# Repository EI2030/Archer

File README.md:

Archer is the codename of our 1st EPD laptop prototype with custom-designed motherboard and 3D-printed chassis.

# Specifications

The specification listed are preliminary and subject to change. Note this is only the specification for the prototype, it does **not** represent the spec for the final product.

- SoC: NXP i.MX 7Dual (2x ARM Cortex-A7 @ 1.2GHz)
- RAM: 2x Micron MT41K256M16 (1GB in total, DDR3)
- Flash: None (prototype designed to always boots from TF card)
- HDD: None
- Network: RTL8273BS (802.11n + BT)
- Main Screen: E Ink ED103TC2 (10.3" 1872x1404) with capactive touch screen
- Sub Screen: ER-TFT0784-1 (7.84" 1280x400) with capactive touch screen
- Screen Controller: i.MX7 integrated EPDC
- Battery: 2x User replaceable LiFePO4 18650 battery
- EC: LPC55S28
- Ports:
  - USB 2.0 Type A Host x1
  - USB 2.0 Type C UFP with Power Delivery x1
  - USB 2.0 Micro B Serial Debug Console x1
  - TF card slot

# Goals

## Goals of this prototype

- Proof of Concept of a EPD laptop
- Enable early development of EC firmware
- Enable early development of the user software
- Test chassis design ideas
- Verify peripheral circuit design
- Enable future prototype with final processor choice

## Non-Goals

- Archer will not represent the performance level of the final product
- Archer is not optimized for low power consumption

# Progress

## Chassis

R0.1 chassis design in progress. Not yet printed.

## Motherboard

R0.1 PCB design finished. Sent to fab.

# Legalese

E Ink® is a registered trademark by E Ink Corporation. All other trademarks are property of their respective owner.

# License

The hardware design is released under the CERN Open Source Hardware License strongly-reciprocal variant, CERN-OHL-S. A copy of the license is provided in the source repository. Additionally, user guide of the license is provided on ohwr.org.

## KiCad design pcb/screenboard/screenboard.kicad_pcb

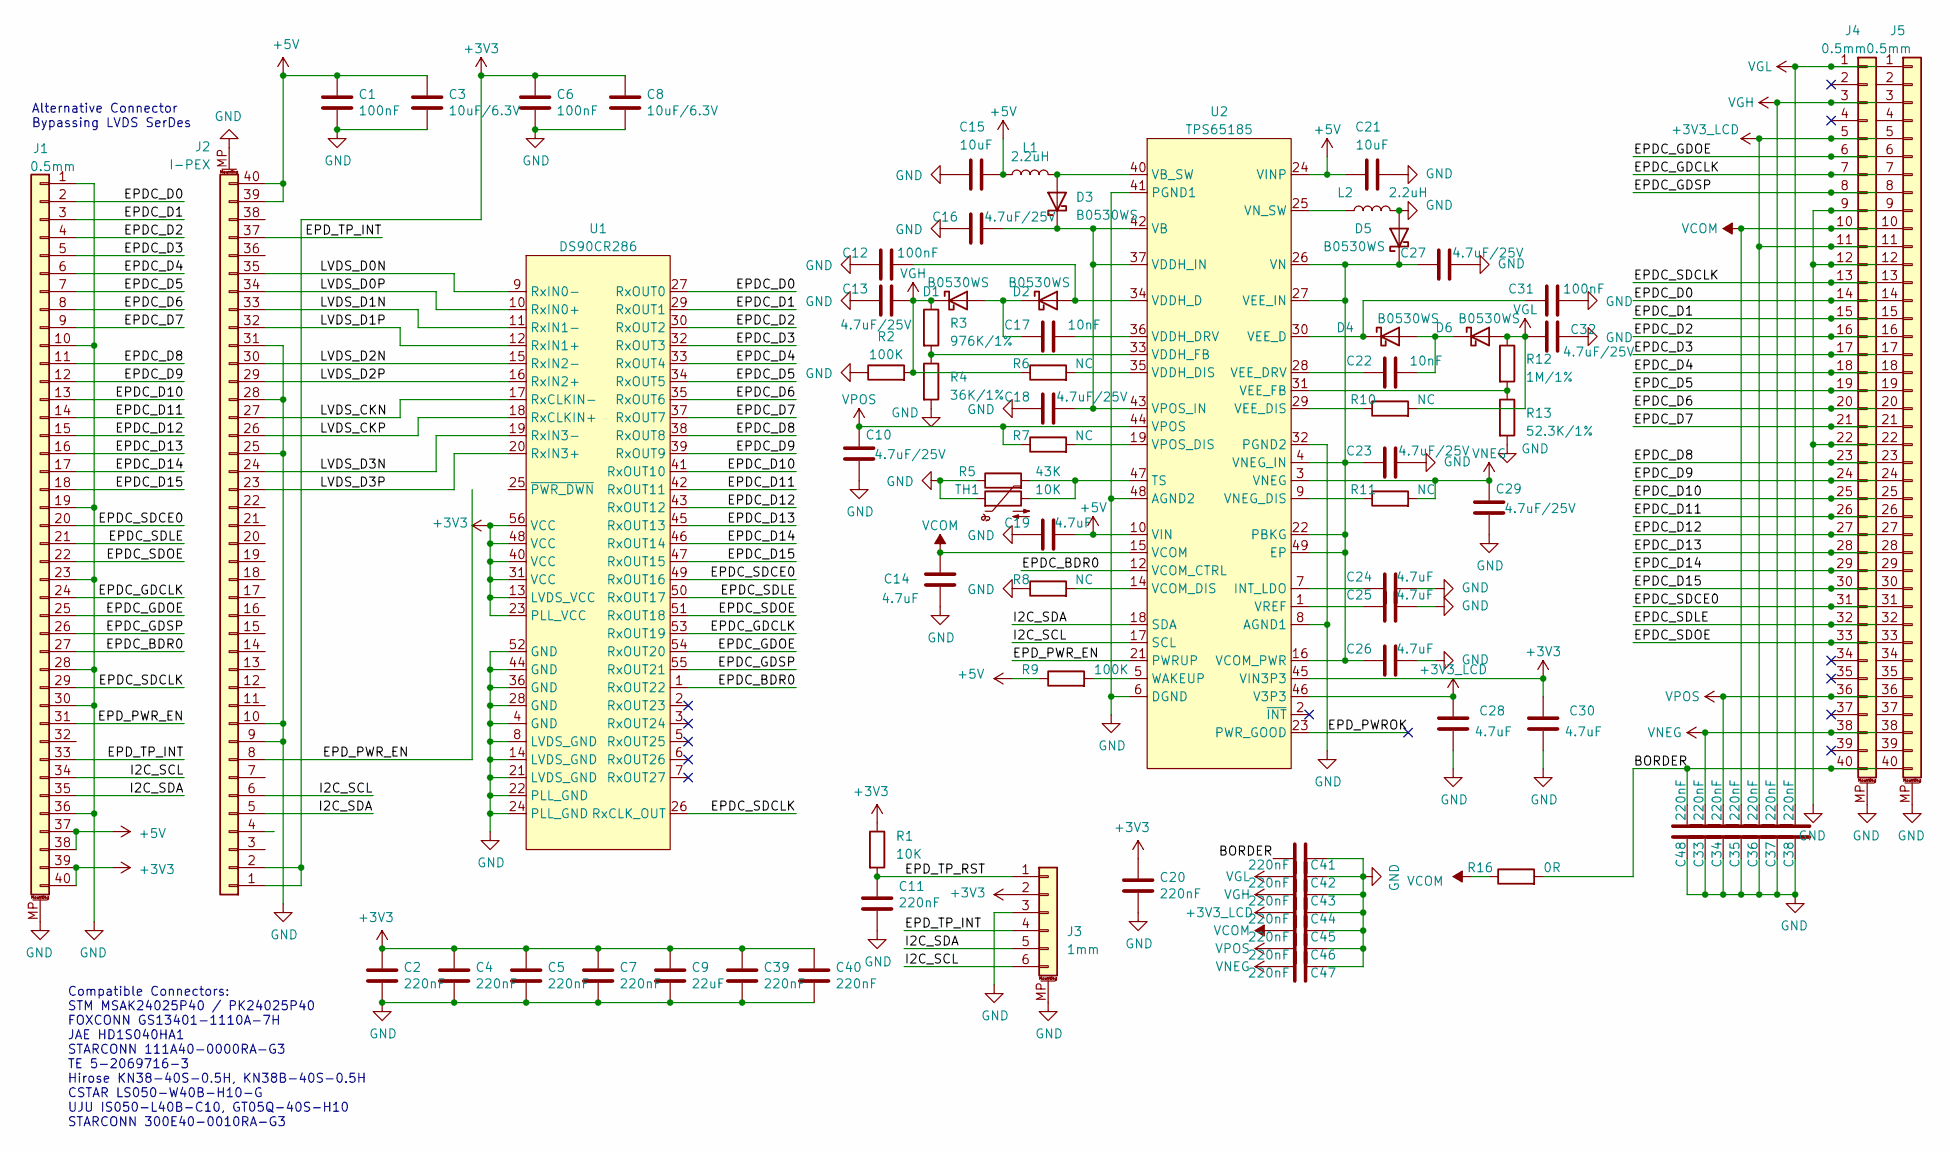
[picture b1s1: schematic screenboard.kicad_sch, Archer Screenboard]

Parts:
C1, C6, C12, C31: 100nF; C_0402_1005Metric
C2, C4, C5, C7, C11, C20, C33, C34, C35, C36, C37, C38, C39, C40, C41, C42, C43, C44, C45, C46, C47, C48: 220nF; C_0402_1005Metric
C3, C8: 10uF/6.3V; C_0603_1608Metric
C9: 22uF; C_0603_1608Metric
C10, C13, C16, C18, C23, C27, C29, C32: 4.7uF/25V; C_0805_2012Metric
C14, C19, C24, C25, C26, C28, C30: 4.7uF; C_0603_1608Metric
C15, C21: 10uF; C_0603_1608Metric
C17, C22: 10nF; C_0402_1005Metric
D1, D2, D3, D4, D5, D6: B0530WS; D_SOD-323
J1: 0.5mm; Hirose_FH12-40S-0.5SH_1x40-1MP_P0.50mm_Horizontal
J2: I-PEX; TE_5-2069716-3_1x40-1MP_P0.5mm_Horizontal
J3: 1mm; Molex_200528-0060_1x06-1MP_P1.00mm_Horizontal_Reversed
J4, J5: 0.5mm; Hirose_FH12-40S-0.5SH_1x40-1MP_P0.50mm_Horizontal_Reversed
L1, L2: 2.2uH; L_Vishay_IHLP-1212
R1: 10K; R_0402_1005Metric
R2, R9: 100K; R_0402_1005Metric
R3: 976K/1%; R_0402_1005Metric
R4: 36K/1%; R_0402_1005Metric
R5: 43K; R_0402_1005Metric
R6, R7, R8, R10, R11: NC; R_0402_1005Metric
R12: 1M/1%; R_0402_1005Metric
R13: 52.3K/1%; R_0402_1005Metric
R16: 0R; R_0402_1005Metric
TH1: 10K; R_0402_1005Metric
U1: DS90CR286; TSSOP-56_6.1x14mm_P0.5mm
U2: TPS65185; QFN-48-1EP_7x7mm_P0.5mm_EP4.1x4.1mm_ThermalVias

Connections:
+3V3: C2.1, C4.1, C5.1, C6.1, C7.1, C8.1, C9.1, C20.1, C30.1, C39.1, C40.1, J1.39, J1.40, J2.1, J2.2, J3.2, R1.1, U1.13 (LVDS_VCC), U1.23 (PLL_VCC), U1.31 (VCC), U1.40 (VCC), U1.48 (VCC), U1.56 (VCC), U2.45 (VIN3P3)
+3V3_LCD: C28.1, C36.1, C44.1, J4.5, J4.11, J5.5, J5.11, U2.46 (V3P3)
+5V: C1.1, C3.1, C15.2, C19.2, C21.1, J1.37, J1.38, J2.39, J2.40, L1.1, R9.1, U2.10 (VIN), U2.24 (VINP)
/BORDER: C41.1, C48.1, J4.40, J5.40, R16.2
/EPDC_BDR0: J1.27, U1.1 (RxOUT22), U2.12 (VCOM_CTRL)
/EPDC_D0: J1.2, J4.14, J5.14, U1.27 (RxOUT0)
/EPDC_D1: J1.3, J4.15, J5.15, U1.29 (RxOUT1)
/EPDC_D2: J1.4, J4.16, J5.16, U1.30 (RxOUT2)
/EPDC_D3: J1.5, J4.17, J5.17, U1.32 (RxOUT3)
/EPDC_D4: J1.6, J4.18, J5.18, U1.33 (RxOUT4)
/EPDC_D5: J1.7, J4.19, J5.19, U1.34 (RxOUT5)
/EPDC_D6: J1.8, J4.20, J5.20, U1.35 (RxOUT6)
/EPDC_D7: J1.9, J4.21, J5.21, U1.37 (RxOUT7)
/EPDC_D8: J1.11, J4.23, J5.23, U1.38 (RxOUT8)
/EPDC_D9: J1.12, J4.24, J5.24, U1.39 (RxOUT9)
/EPDC_D10: J1.13, J4.25, J5.25, U1.41 (RxOUT10)
/EPDC_D11: J1.14, J4.26, J5.26, U1.42 (RxOUT11)
/EPDC_D12: J1.15, J4.27, J5.27, U1.43 (RxOUT12)
/EPDC_D13: J1.16, J4.28, J5.28, U1.45 (RxOUT13)
/EPDC_D14: J1.17, J4.29, J5.29, U1.46 (RxOUT14)
/EPDC_D15: J1.18, J4.30, J5.30, U1.47 (RxOUT15)
/EPDC_GDCLK: J1.24, J4.7, J5.7, U1.53 (RxOUT19)
/EPDC_GDOE: J1.25, J4.6, J5.6, U1.54 (RxOUT20)
/EPDC_GDSP: J1.26, J4.8, J5.8, U1.55 (RxOUT21)
/EPDC_SDCE0: J1.20, J4.31, J5.31, U1.49 (RxOUT16)
/EPDC_SDCLK: J1.29, J4.13, J5.13, U1.26 (RxCLK_OUT)
/EPDC_SDLE: J1.21, J4.32, J5.32, U1.50 (RxOUT17)
/EPDC_SDOE: J1.22, J4.33, J5.33, U1.51 (RxOUT18)
/EPD_PWR_EN: J1.31, J2.8, U2.21 (PWRUP)
/EPD_TP_INT: J1.33, J2.37, J3.4
/EPD_TP_RST: C11.1, J3.1, R1.2
/I2C_SCL: J1.34, J2.6, J3.6, U2.17 (SCL)
/I2C_SDA: J1.35, J2.5, J3.5, U2.18 (SDA)
/LVDS_CKN: J2.27, U1.17 (RxCLKIN-)
/LVDS_CKP: J2.26, U1.18 (RxCLKIN+)
/LVDS_D0N: J2.35, U1.9 (RxIN0-)
/LVDS_D0P: J2.34, U1.10 (RxIN0+)
/LVDS_D1N: J2.33, U1.11 (RxIN1-)
/LVDS_D1P: J2.32, U1.12 (RxIN1+)
/LVDS_D2N: J2.30, U1.15 (RxIN2-)
/LVDS_D2P: J2.29, U1.16 (RxIN2+)
/LVDS_D3N: J2.24, U1.19 (RxIN3-)
/LVDS_D3P: J2.23, U1.20 (RxIN3+)
GND: C1.2, C2.2, C3.2, C4.2, C5.2, C6.2, C7.2, C8.2, C9.2, C10.1, C11.2, C12.1, C13.1, C14.1, C15.1, C16.1, C18.1, C19.1, C20.2, C21.2, C23.2, C24.2, C25.2, C26.2, C27.2, C28.2, C29.1, C30.2, C31.2, C32.1, C33.2, C34.2, C35.2, C36.2, C37.2, C38.2, C39.2, C40.2, C41.2, C42.2, C43.2, C44.2, C45.2, C46.2, C47.2, C48.2, D5.2 (A), J1.1, J1.10, J1.19, J1.23, J1.28, J1.30, J1.36, J1.MP (MountPin), J2.9, J2.10, J2.25, J2.28, J2.31, J2.MP (MountPin), J3.3, J3.MP (MountPin), J4.9, J4.12, J4.22, J4.MP (MountPin), J5.9, J5.12, J5.22, J5.MP (MountPin), L2.2, R2.1, R4.2, R5.1, R8.1, R13.2, TH1.1, U1.4 (GND), U1.8 (LVDS_GND), U1.14 (LVDS_GND), U1.21 (LVDS_GND), U1.22 (PLL_GND), U1.24 (PLL_GND), U1.28 (GND), U1.36 (GND), U1.44 (GND), U1.52 (GND), U2.6 (DGND), U2.8 (AGND1), U2.32 (PGND2), U2.41 (PGND1), U2.48 (AGND2)
unnamed: C12.2, D2.2 (A), U2.34 (VDDH_D)
unnamed: C16.2, C18.2, D3.1 (K), U2.37 (VDDH_IN), U2.42 (VB), U2.43 (VPOS_IN)
unnamed: C17.1, D1.2 (A), D2.1 (K)
unnamed: C17.2, U2.36 (VDDH_DRV)
unnamed: C22.1, U2.28 (VEE_DRV)
unnamed: C22.2, D4.2 (A), D6.1 (K)
unnamed: C23.1, C26.1, C27.1, D5.1 (K), U2.4 (VNEG_IN), U2.16 (VCOM_PWR), U2.22 (PBKG), U2.26 (VN), U2.27 (VEE_IN), U2.49 (EP)
unnamed: C24.1, U2.7 (INT_LDO)
unnamed: C25.1, U2.1 (VREF)
unnamed: C31.1, D4.1 (K), U2.30 (VEE_D)
unnamed: D3.2 (A), L1.2, U2.40 (VB_SW)
unnamed: L2.1, U2.25 (VN_SW)
unnamed: R3.2, R4.1, U2.33 (VDDH_FB)
unnamed: R5.2, TH1.2, U2.47 (TS)
unnamed: R6.2, U2.35 (VDDH_DIS)
unnamed: R7.2, U2.19 (VPOS_DIS)
unnamed: R8.2, U2.14 (VCOM_DIS)
unnamed: R9.2, U2.5 (WAKEUP)
unnamed: R10.1, U2.29 (VEE_DIS)
unnamed: R11.1, U2.9 (VNEG_DIS)
unnamed: R12.2, R13.1, U2.31 (VEE_FB)
VCOM: C14.2, C35.1, C45.1, J4.10, J5.10, R16.1, U2.15 (VCOM)
VGH: C13.2, C37.1, C43.1, D1.1 (K), J4.3, J5.3, R2.2, R3.1, R6.1
VGL: C32.2, C38.1, C42.1, D6.2 (A), J4.1, J5.1, R10.2, R12.1
VNEG: C29.2, C33.1, C47.1, J4.38, J5.38, R11.2, U2.3 (VNEG)
VPOS: C10.2, C34.1, C46.1, J4.36, J5.36, R7.1, U2.44 (VPOS)

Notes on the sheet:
Alternative Connector Bypassing LVDS SerDes
Compatible Connectors: STM MSAK24025P40 / PK24025P40 FOXCONN GS13401-1110A-7H JAE HD1S040HA1 STARCONN 111A40-0000RA-G3 TE 5-2069716-3 Hirose KN38-40S-0.5H, KN38B-40S-0.5H CSTAR LS050-W40B-H10-G UJU IS050-L40B-C10, GT05Q-40S-H10 STARCONN 300E40-0010RA-G3

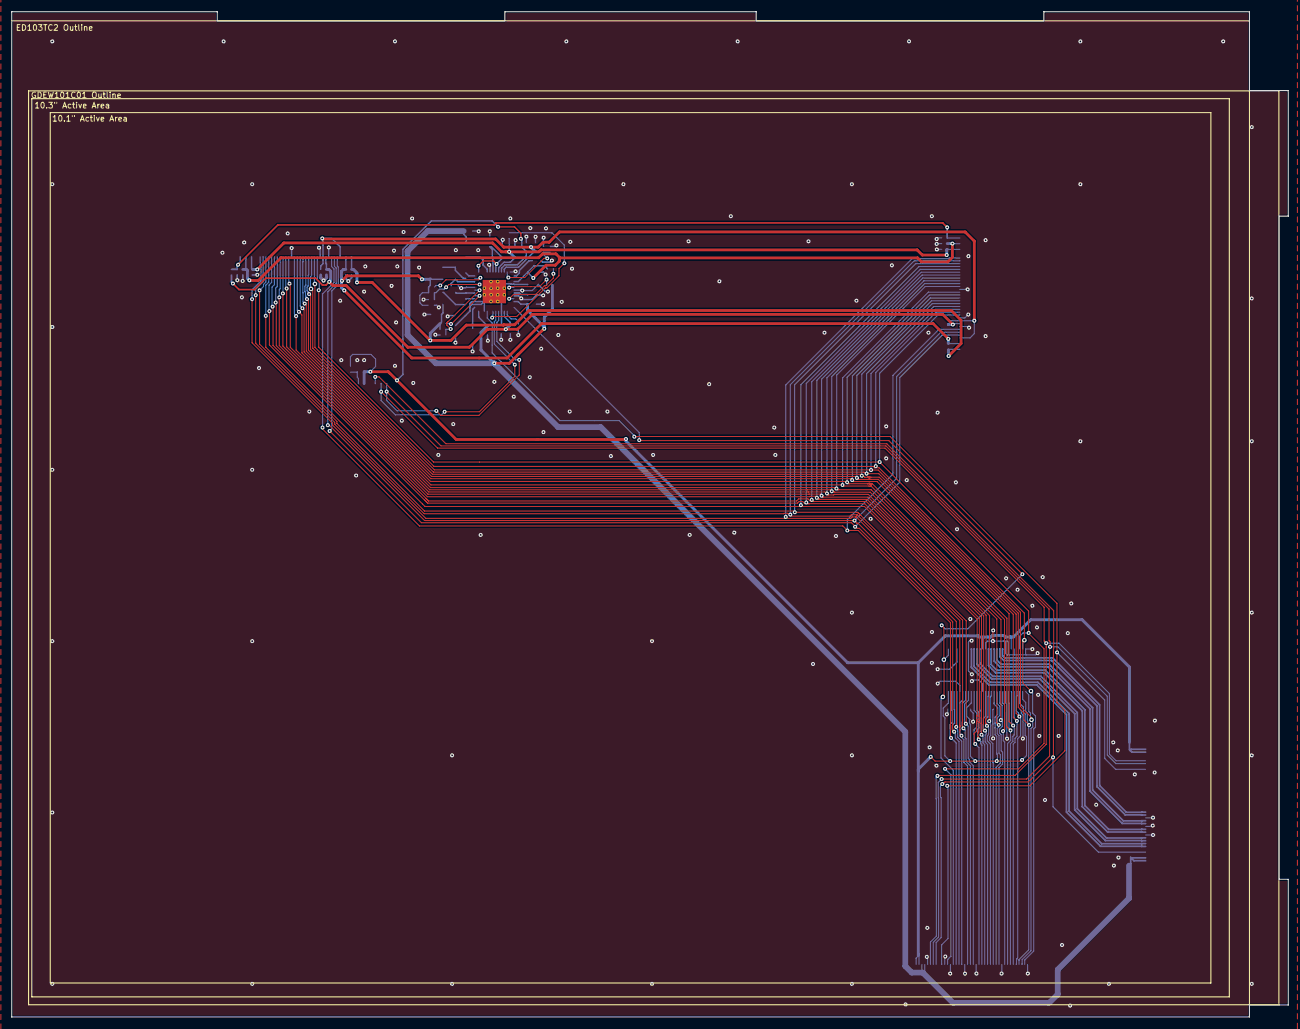
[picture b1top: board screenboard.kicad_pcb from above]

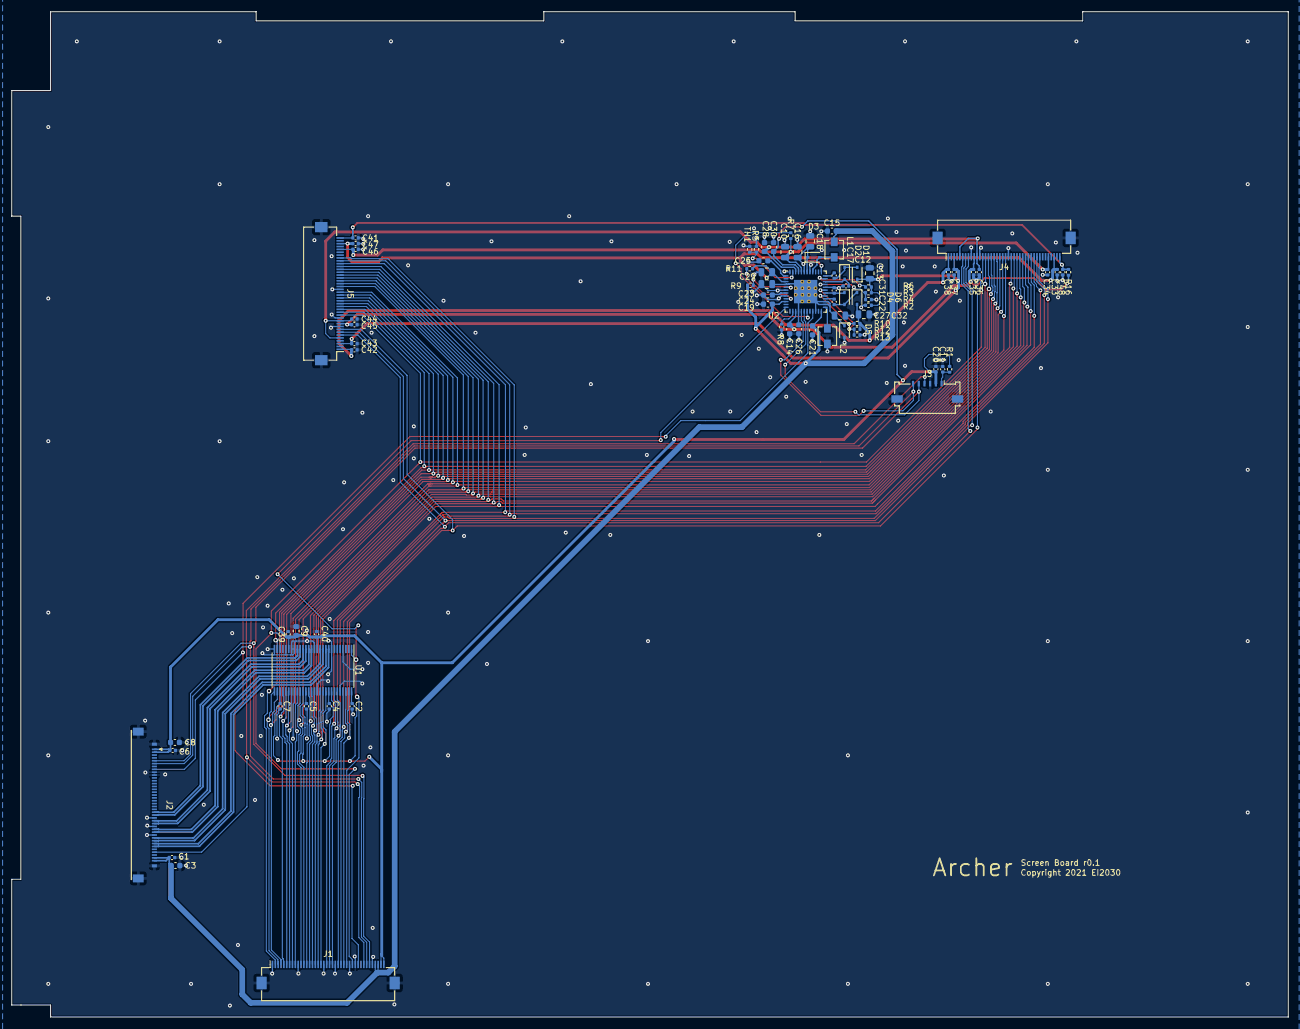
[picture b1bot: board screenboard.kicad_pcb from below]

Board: 2 copper layers, 223.5 x 176.0 mm, 78 parts (78 on the bottom side), 70 nets.

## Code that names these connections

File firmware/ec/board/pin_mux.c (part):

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mcu_data: ksdk2_0
processor_version: 9.0.1
pin_labels:
- {pin_num: '54', pin_signal: PIO0_0/FC3_SCK/CTIMER0_MAT0/SCT_GPI0/SD1_CARD_INT_N/SECURE_GPIO0_0/ACMP0_A, label: KSI0, identifier: KSI0}
- {pin_num: '7', pin_signal: PIO0_1/FC3_CTS_SDA_SSEL0/CT_INP0/SCT_GPI1/SD1_CLK/CMP0_OUT/SECURE_GPIO0_1, label: KSI1, identifier: KSI1}
- {pin_num: '81', pin_signal: PIO0_2/FC3_TXD_SCL_MISO_WS/CT_INP1/SCT0_OUT0/SCT_GPI2/SECURE_GPIO0_2, label: KSI2, identifier: KSI2}
- {pin_num: '83', pin_signal: PIO0_3/FC3_RXD_SDA_MOSI_DATA/CTIMER0_MAT1/SCT0_OUT1/SCT_GPI3/SECURE_GPIO0_3, label: KSI3, identifier: KSI3}
- {pin_num: '86', pin_signal: PIO0_4/FC4_SCK/CT_INP12/SCT_GPI4/FC3_CTS_SDA_SSEL0/SECURE_GPIO0_4, label: KSI4, identifier: KSI4}
- {pin_num: '88', pin_signal: PIO0_5/FC4_RXD_SDA_MOSI_DATA/CTIMER3_MAT0/SCT_GPI5/FC3_RTS_SCL_SSEL1/MCLK/SECURE_GPIO0_5, label: KSI5, identifier: KSI5}
- {pin_num: '89', pin_signal: PIO0_6/FC3_SCK/CT_INP13/CTIMER4_MAT0/SCT_GPI6/SECURE_GPIO0_6, label: KSI6, identifier: KSI6}
- {pin_num: '6', pin_signal: PIO0_7/FC3_RTS_SCL_SSEL1/SD0_CLK/FC5_SCK/FC1_SCK/SECURE_GPIO0_7, label: KSI7, identifier: KSI7}
- {pin_num: '26', pin_signal: PIO0_8/FC3_SSEL3/SD0_CMD/FC5_RXD_SDA_MOSI_DATA/SWO/SECURE_GPIO0_8, label: PMIC_STBY_REQ, identifier: PMIC_STBY_REQ}
- {pin_num: '55', pin_signal: PIO0_9/FC3_SSEL2/SD0_POW_EN/FC5_TXD_SCL_MISO_WS/SECURE_GPIO0_9/ACMP0_B, label: PMIC_ON_REQ, identifier: PMIC_ON_REQ}
- {pin_num: '21', pin_signal: PIO0_10/FC6_SCK/CT_INP10/CTIMER2_MAT0/FC1_TXD_SCL_MISO_WS/SCT0_OUT2/SWO/SECURE_GPIO0_10/ADC0_1, label: LED, identifier: LED}
- {pin_num: '71', pin_signal: PIO0_13/FC1_CTS_SDA_SSEL0/UTICK_CAP0/CT_INP0/SCT_GPI0/FC1_RXD_SDA_MOSI_DATA/PLU_IN0/SECURE_GPIO0_13, label: SDA, identifier: SDA}
- {pin_num: '72', pin_signal: PIO0_14/FC1_RTS_SCL_SSEL1/UTICK_CAP1/CT_INP1/SCT_GPI1/FC1_TXD_SCL_MISO_WS/PLU_IN1/SECURE_GPIO0_14, label: SCL, identifier: SCL}
- {pin_num: '22', pin_signal: PIO0_15/FC6_CTS_SDA_SSEL0/UTICK_CAP2/CT_INP16/SCT0_OUT2/SD0_WR_PRT/SECURE_GPIO0_15/ADC0_2, label: MPU_RST, identifier: MPU_RST}
- {pin_num: '56', pin_signal: PIO0_18/FC4_CTS_SDA_SSEL0/SD0_WR_PRT/CTIMER1_MAT0/SCT0_OUT1/PLU_IN3/SECURE_GPIO0_18/ACMP0_C, label: KSOS0, identifier: KSOS0}
- {pin_num: '90', pin_signal: PIO0_19/FC4_RTS_SCL_SSEL1/UTICK_CAP0/CTIMER0_MAT2/SCT0_OUT2/FC7_TXD_SCL_MISO_WS/PLU_IN4/SECURE_GPIO0_19, label: KSOS1, identifier: KSOS1}
- {pin_num: '74', pin_signal: PIO0_20/FC3_CTS_SDA_SSEL0/CTIMER1_MAT1/CT_INP15/SCT_GPI2/FC7_RXD_SDA_MOSI_DATA/HS_SPI_SSEL0/PLU_IN5/SECURE_GPIO0_20/FC4_TXD_SCL_MISO_WS,
  label: KSOS2, identifier: KSOS2}
- {pin_num: '76', pin_signal: PIO0_21/FC3_RTS_SCL_SSEL1/UTICK_CAP3/CTIMER3_MAT3/SCT_GPI3/FC7_SCK/PLU_CLKIN/SECURE_GPIO0_21, label: KSOS3, identifier: KSOS3}
- {pin_num: '78', pin_signal: PIO0_22/FC6_TXD_SCL_MISO_WS/UTICK_CAP1/CT_INP15/SCT0_OUT3/USB0_VBUS/SD1_D0/PLU_OUT7/SECURE_GPIO0_22, label: KSOE, identifier: KSOE}
- {pin_num: '70', pin_signal: PIO0_24/FC0_RXD_SDA_MOSI_DATA/SD0_D0/CT_INP8/SCT_GPI0/SECURE_GPIO0_24, label: SPI_SCLK, identifier: SPI_SCLK}
- {pin_num: '20', pin_signal: PIO0_23/MCLK/CTIMER1_MAT2/CTIMER3_MAT3/SCT0_OUT4/FC0_CTS_SDA_SSEL0/SD1_D1/SECURE_GPIO0_23/ADC0_0, label: SPI_CS, identifier: SPI_CS}
- {pin_num: '66', pin_signal: PIO0_28/FC0_SCK/SD1_CMD/CT_INP11/SCT0_OUT7/USB0_OVERCURRENTN/PLU_OUT1/SECURE_GPIO0_28, label: LCD_EN, identifier: SPI_;LCD_EN}
- {pin_num: '79', pin_signal: PIO0_25/FC0_TXD_SCL_MISO_WS/SD0_D1/CT_INP9/SCT_GPI1/SECURE_GPIO0_25, label: SPI_MOSI, identifier: SPI_MOSI}
- {pin_num: '60', pin_signal: PIO0_26/FC2_RXD_SDA_MOSI_DATA/CLKOUT/CT_INP14/SCT0_OUT5/USB0_IDVALUE/FC0_SCK/HS_SPI_MOSI/SECURE_GPIO0_26, label: SPI_MISO, identifier: SPI_MISO}
- {pin_num: '92', pin_signal: PIO0_29/FC0_RXD_SDA_MOSI_DATA/SD1_D2/CTIMER2_MAT3/SCT0_OUT8/CMP0_OUT/PLU_OUT2/SECURE_GPIO0_29, label: UART_RX, identifier: UART_RX}
- {pin_num: '94', pin_signal: PIO0_30/FC0_TXD_SCL_MISO_WS/SD1_D3/CTIMER0_MAT0/SCT0_OUT9/SECURE_GPIO0_30, label: UART_TX, identifier: UART_TX}
- {pin_num: '11', pin_signal: PIO1_0/FC0_RTS_SCL_SSEL1/SD0_D3/CT_INP2/SCT_GPI4/PLU_OUT3/ADC0_11, label: USB_OTG_ID, identifier: USB_OTG_ID}
- {pin_num: '59', pin_signal: PIO1_1/FC3_RXD_SDA_MOSI_DATA/CT_INP3/SCT_GPI5/HS_SPI_SSEL1/USB1_OVERCURRENTN/PLU_OUT4, label: EC_INT, identifier: EC_INT}
- {pin_num: '61', pin_signal: PIO1_2/CTIMER0_MAT3/SCT_GPI6/HS_SPI_SCK/USB1_PORTPWRN/PLU_OUT5, label: PWR_EN, identifier: PWR_EN}
- {pin_num: '62', pin_signal: PIO1_3/SCT0_OUT4/HS_SPI_MISO/USB0_PORTPWRN/PLU_OUT6, label: ARM_EN, identifier: ARM_EN}
 * BE CAREFUL MODIFYING THIS COMMENT - IT IS YAML SETTINGS FOR TOOLS ***********
 */
/* clang-format on */
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- pin_list:
  - {pin_num: '54', peripheral: GPIO, signal: 'PIO0, 0', pin_signal: PIO0_0/FC3_SCK/CTIMER0_MAT0/SCT_GPI0/SD1_CARD_INT_N/SECURE_GPIO0_0/ACMP0_A, direction: INPUT}
  - {pin_num: '81', peripheral: GPIO, signal: 'PIO0, 2', pin_signal: PIO0_2/FC3_TXD_SCL_MISO_WS/CT_INP1/SCT0_OUT0/SCT_GPI2/SECURE_GPIO0_2, direction: INPUT}
  - {pin_num: '7', peripheral: GPIO, signal: 'PIO0, 1', pin_signal: PIO0_1/FC3_CTS_SDA_SSEL0/CT_INP0/SCT_GPI1/SD1_CLK/CMP0_OUT/SECURE_GPIO0_1, direction: INPUT}
  - {pin_num: '83', peripheral: GPIO, signal: 'PIO0, 3', pin_signal: PIO0_3/FC3_RXD_SDA_MOSI_DATA/CTIMER0_MAT1/SCT0_OUT1/SCT_GPI3/SECURE_GPIO0_3, direction: INPUT}
  - {pin_num: '86', peripheral: GPIO, signal: 'PIO0, 4', pin_signal: PIO0_4/FC4_SCK/CT_INP12/SCT_GPI4/FC3_CTS_SDA_SSEL0/SECURE_GPIO0_4, direction: INPUT}
  - {pin_num: '88', peripheral: GPIO, signal: 'PIO0, 5', pin_signal: PIO0_5/FC4_RXD_SDA_MOSI_DATA/CTIMER3_MAT0/SCT_GPI5/FC3_RTS_SCL_SSEL1/MCLK/SECURE_GPIO0_5, direction: INPUT}
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  - {pin_num: '70', peripheral: GPIO, signal: 'PIO0, 24', pin_signal: PIO0_24/FC0_RXD_SDA_MOSI_DATA/SD0_D0/CT_INP8/SCT_GPI0/SECURE_GPIO0_24, direction: OUTPUT}
  - {pin_num: '20', peripheral: GPIO, signal: 'PIO0, 23', pin_signal: PIO0_23/MCLK/CTIMER1_MAT2/CTIMER3_MAT3/SCT0_OUT4/FC0_CTS_SDA_SSEL0/SD1_D1/SECURE_GPIO0_23/ADC0_0,
    direction: OUTPUT}
  - {pin_num: '66', peripheral: GPIO, signal: 'PIO0, 28', pin_signal: PIO0_28/FC0_SCK/SD1_CMD/CT_INP11/SCT0_OUT7/USB0_OVERCURRENTN/PLU_OUT1/SECURE_GPIO0_28, identifier: LCD_EN,
    direction: OUTPUT}
  - {pin_num: '79', peripheral: GPIO, signal: 'PIO0, 25', pin_signal: PIO0_25/FC0_TXD_SCL_MISO_WS/SD0_D1/CT_INP9/SCT_GPI1/SECURE_GPIO0_25, direction: OUTPUT}
  - {pin_num: '60', peripheral: GPIO, signal: 'PIO0, 26', pin_signal: PIO0_26/FC2_RXD_SDA_MOSI_DATA/CLKOUT/CT_INP14/SCT0_OUT5/USB0_IDVALUE/FC0_SCK/HS_SPI_MOSI/SECURE_GPIO0_26,
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

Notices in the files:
pcb/mainboard/pcb.kicad_pcb:
Copyright EI-2030 2021. / Engineer: Wenting Zhang
This source describes Open Hardware and is licensed under the CERN-OHL-S v2.
Copyright 2021 EI2030
